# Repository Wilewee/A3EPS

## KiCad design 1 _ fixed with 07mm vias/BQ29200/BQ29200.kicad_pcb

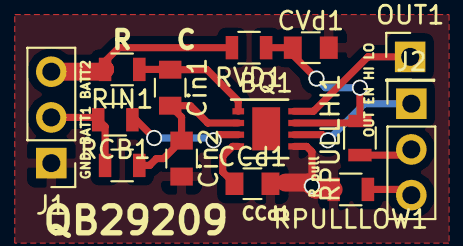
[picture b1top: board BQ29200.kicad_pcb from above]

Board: 2 copper layers, 14 parts (0 on the bottom side), 12 nets.

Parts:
BQ1: BQ29209; DFN-8-1EP_3x3mm_Pitch0.65mm
CCd1: .1u; C_0805
CVd1: .1u; C_0805
Cin1, Cin2: .1u; C_0805
J1, J2: CONN_01X03; Socket_Strip_Straight_1x03_Pitch2.54mm
OUT1: CONN_01X01; Socket_Strip_Straight_1x01_Pitch2.54mm
RCB1: 120; R_0805
RIN1, RIN2: 1k; R_0805
RPULLHI1: R; R_0805
RPULLLOW1: R; R_0805
RVD1: 100; R_0805

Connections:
GND: BQ1.5, CCd1.2, CVd1.2, Cin2.2, J1.1, RPULLLOW1.2
unnamed: BQ1.1, Cin1.1, RIN1.1
unnamed: BQ1.2, Cin1.2, Cin2.1, RIN2.1
unnamed: BQ1.3, RCB1.1
unnamed: BQ1.4, CCd1.1
unnamed: BQ1.6, J2.1
unnamed: BQ1.7, CVd1.1, RPULLHI1.2, RVD1.1
unnamed: BQ1.8, OUT1.1
unnamed: J1.2, RCB1.2, RIN2.2
unnamed: J1.3, RIN1.2, RVD1.2
unnamed: J2.2, RPULLHI1.1
unnamed: J2.3, RPULLLOW1.1

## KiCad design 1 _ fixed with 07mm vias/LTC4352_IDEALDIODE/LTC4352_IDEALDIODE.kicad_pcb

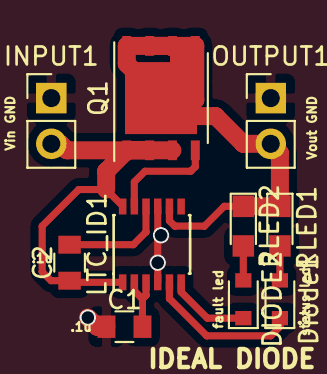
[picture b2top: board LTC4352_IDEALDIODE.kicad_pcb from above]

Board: 2 copper layers, 10 parts (0 on the bottom side), 10 nets.

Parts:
C1, C2: .1u; C_0805
DIODE2: LED; D_0805
Diode1: LED; D_0805
INPUT1: CONN_01X02; Socket_Strip_Straight_1x02_Pitch2.54mm
LTC_ID1: LTC4352; MSOP-12_3x4mm_Pitch0.65mm
OUTPUT1: CONN_01X02; Socket_Strip_Straight_1x02_Pitch2.54mm
Q1: FDMS8050; DFN-8-1EP_6x5mm_Pitch1.27mm_LargeFlag
RLED1, RLED2: 4.7k; LED_0805

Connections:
GND: C1.1, INPUT1.1, LTC_ID1.4, LTC_ID1.7, LTC_ID1.9, OUTPUT1.1
unnamed: C1.2, LTC_ID1.2, LTC_ID1.3
unnamed: C2.1, INPUT1.2, LTC_ID1.1, LTC_ID1.12, Q1.1, Q1.2, Q1.3
unnamed: C2.2, LTC_ID1.10
unnamed: DIODE2.1, LTC_ID1.6
unnamed: DIODE2.2, RLED2.2
unnamed: Diode1.1, LTC_ID1.5
unnamed: Diode1.2, RLED1.2
unnamed: LTC_ID1.8, OUTPUT1.2, Q1.5, Q1.6, Q1.7, Q1.8, RLED1.1, RLED2.1
unnamed: LTC_ID1.11, Q1.4

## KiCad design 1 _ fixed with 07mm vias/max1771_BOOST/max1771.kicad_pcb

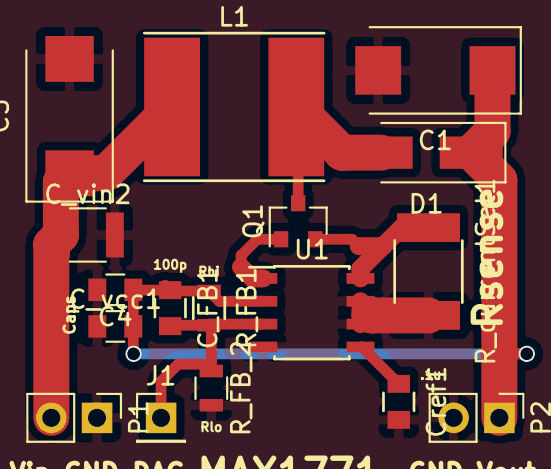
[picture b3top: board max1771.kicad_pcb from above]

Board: 2 copper layers, 17 parts (0 on the bottom side), 8 nets.

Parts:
C1, C5: CP; CP_Tantalum_Case-D_EIA-7343-31_Reflow
C4: C; C_0805
C_FB1: 100p; C_0805
C_vcc1: 1u; C_0805
C_vin2: BIG; C_1210
Cref1: 0.1u; C_0805
D1: D_Schottky_Small; SMA_Handsoldering
J1: CONN_01X01; Socket_Strip_Straight_1x01_Pitch2.54mm
L1: INDUCTOR; Inductor_Taiyo-Yuden_NR-80xx_HandSoldering
P1: Input_conn; Socket_Strip_Straight_1x02_Pitch2.54mm
P2: CONN_01X02; Socket_Strip_Straight_1x02_Pitch2.54mm
Q1: BS170; SOT-23
R_FB1: R_FB_high; R_0805
R_FB_2: R_FB_LOW; R_0805
R_currentSet1: 0.02; R_1812
U1: MAX1771§; SOIC-8_3.9x4.9mm_Pitch1.27mm

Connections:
GND: C1.2, C4.2, C5.2, C_vcc1.1, C_vin2.2, Cref1.2, P1.1, P2.2, R_FB_2.2, R_currentSet1.2, U1.4, U1.6, U1.7
unnamed: C1.1, C4.1, C_FB1.1, C_vcc1.2, D1.1, P2.1, R_FB1.1, U1.2
unnamed: C5.1, C_vin2.1, L1.1, P1.2
unnamed: C_FB1.2, J1.1, R_FB1.2, R_FB_2.1, U1.3
unnamed: Cref1.1, U1.5
unnamed: D1.2, L1.2, Q1.2
unnamed: Q1.1, U1.1
unnamed: Q1.3, R_currentSet1.1, U1.8

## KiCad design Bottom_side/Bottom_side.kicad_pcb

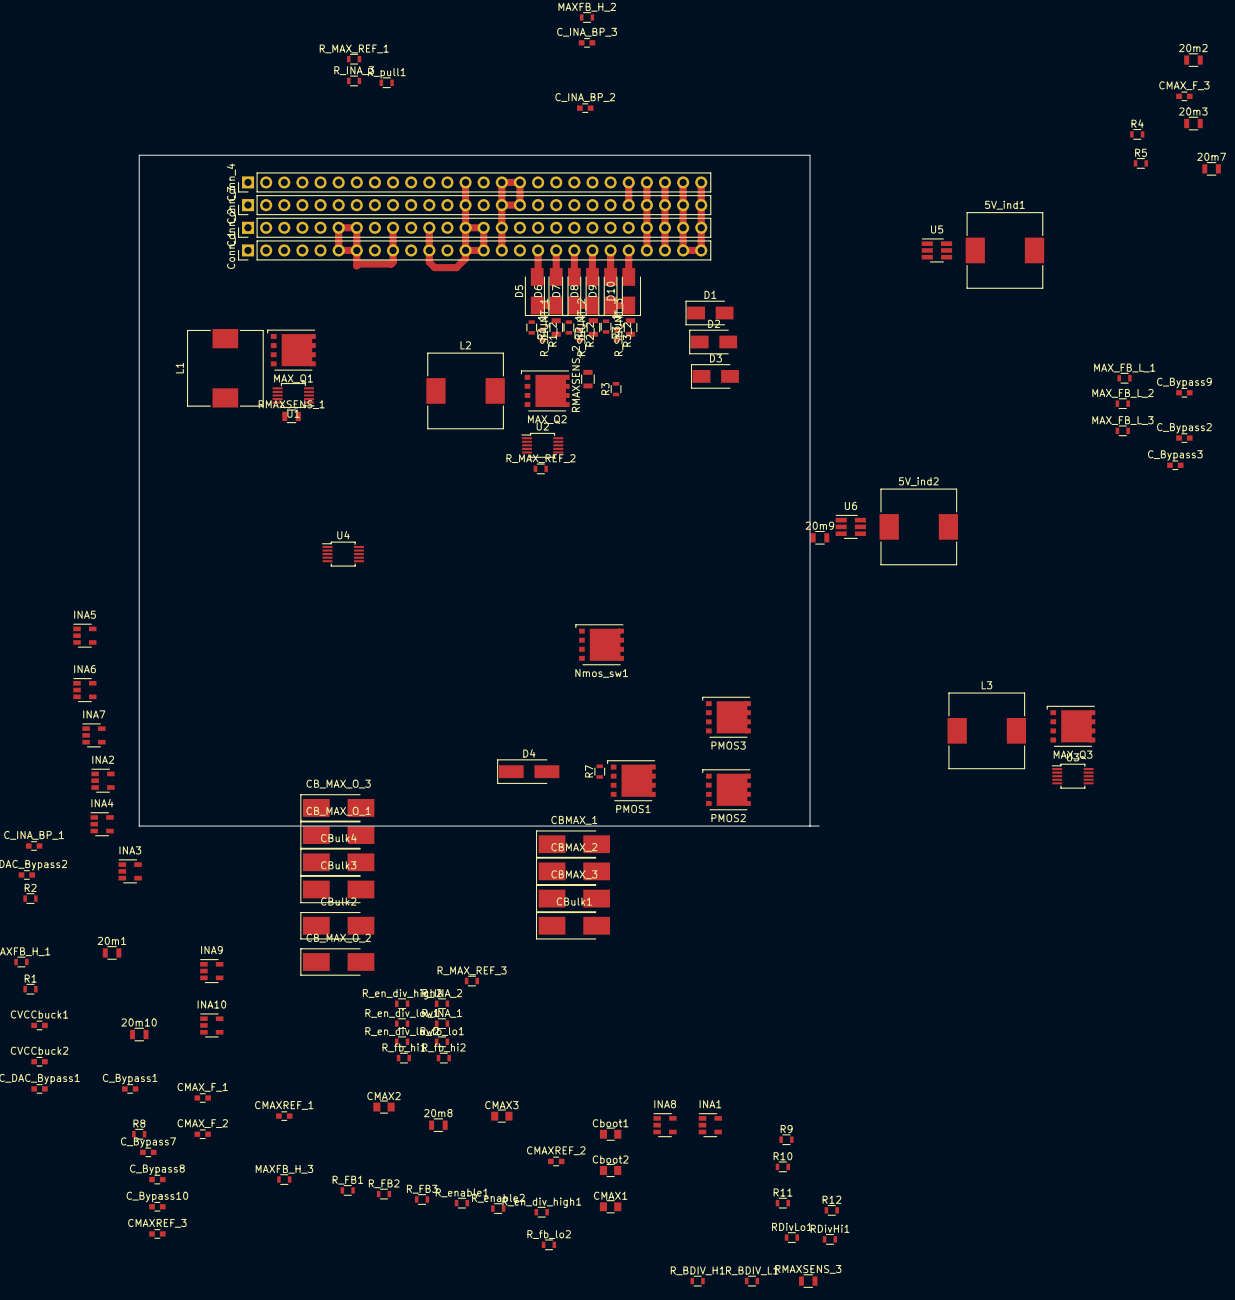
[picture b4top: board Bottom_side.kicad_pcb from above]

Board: 2 copper layers, 95.2 x 94.0 mm, 137 parts (0 on the bottom side), 82 nets.

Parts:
5V_ind1, 5V_ind2: 10u; L_10.4x10.4_H4.8
20m1, 20m2, 20m3, 20m7, 20m8, 20m9, 20m10: R_Shunt; R_0805
CBMAX_1, CBMAX_2, CBMAX_3: 68uF; CP_Tantalum_Case-C_EIA-6032-28_Hand
CB_MAX_O_1, CB_MAX_O_2, CB_MAX_O_3: 68uF; CP_Tantalum_Case-C_EIA-6032-28_Hand
CBulk1, CBulk2, CBulk3, CBulk4: C; CP_Tantalum_Case-C_EIA-6032-28_Hand
CMAX1, CMAX2, CMAX3: 1uF; C_0805
CMAXREF_1, CMAXREF_2, CMAXREF_3: .22uF; C_0603
CMAX_F_1, CMAX_F_2, CMAX_F_3: 220pF; C_0603
CVCCbuck1, CVCCbuck2: 10u; C_0603
C_Bypass1, C_Bypass2, C_Bypass3, C_Bypass7, C_Bypass8, C_Bypass9, C_Bypass10: .1u; C_0603
C_DAC_Bypass1, C_DAC_Bypass2: C; C_0603
C_INA_BP_1, C_INA_BP_2, C_INA_BP_3: .1u; C_0603
Cboot1, Cboot2: .1uF; C_0805
Conn_1, Conn_3: Conn_01x26; Socket_Strip_Straight_1x26_Pitch2.54mm
Conn_2: Conn_2; Socket_Strip_Straight_1x26_Pitch2.54mm
Conn_4: Conn_4; Socket_Strip_Straight_1x26_Pitch2.54mm
D1, D2, D3: D_Schottky; D_SMA
D4: D; D_SMA_Handsoldering
D5, D6, D7, D8, D9, D10: D; D_SMA
INA1, INA2, INA3, INA4, INA5, INA6, INA7, INA8, INA9, INA10: INA139; SOT-23-5
L1, L2, L3: L_Small; L_10.4x10.4_H4.8
MAXFB_H_1, MAXFB_H_2, MAXFB_H_3: 100k; R_0603
MAX_FB_L_1, MAX_FB_L_2, MAX_FB_L_3: 22k; R_0603
MAX_Q1, MAX_Q2, MAX_Q3: Q_NMOS_GDS; TDSON-8-1
Nmos_sw1: Logic level Nch mosfet; TDSON-8-1
PMOS1: PCH GDS; TDSON-8-1
PMOS2, PMOS3: Pch GDS; TDSON-8-1
R1, R2: 10k; R_0603
R1_1, R2_1, R3, R3_1, R4, R5, R9, R10, R11, R12: 100k; R_0603
R1_2, R2_2, R3_2: 200k; R_0603
R7, R8: R; R_0603
RDivHi1: R; R_0603
RDivLo1: R; R_0603
RMAXSENS_1, RMAXSENS_2, RMAXSENS_3: 0.02; R_0805
R_BDIV_H1: 220k; R_0603
R_BDIV_L1: 100k; R_0603
R_FB1, R_FB2, R_FB3: 100k; R_0603
R_INA_1, R_INA_2, R_INA_3: 100k; R_0603
R_MAX_REF_1, R_MAX_REF_2, R_MAX_REF_3: 100k; R_0603
R_SHUNT_1, R_SHUNT_2, R_SHUNT_3: 20m; R_0805
R_en_div_high1, R_en_div_high2: R; R_0603
R_en_div_low1, R_en_div_low2: R; R_0603
R_enable1, R_enable2: R; R_0603
R_fb_hi1, R_fb_hi2: R; R_0603
R_fb_lo1, R_fb_lo2: R; R_0603
R_pull1: R; R_0603
U1, U2, U3: MAX668; MSOP-10_3x3mm_Pitch0.5mm
U4: MCP4728; MSOP-10_3x3mm_Pitch0.5mm
U5, U6: TPS54302; SOT-23-6_Handsoldering

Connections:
/3V3: C_Bypass1.1, C_Bypass2.1, C_Bypass3.1, C_Bypass7.1, C_Bypass8.1, C_Bypass9.1, C_Bypass10.1, C_DAC_Bypass1.1, C_DAC_Bypass2.1, C_INA_BP_1.1, C_INA_BP_2.1, C_INA_BP_3.1, INA1.5, INA2.5, INA3.5, INA4.5, INA5.5, INA6.5, INA7.5, INA8.5, INA9.5, INA10.5, R1.2, R2.2, U4.1
/5V_1: 20m7.1, INA7.4
/5V_2: 20m8.1, INA8.4
/A_1_I: INA1.1, R_INA_1.1
/A_1_O: INA6.1, R5.1
/A_2_I: INA2.1, R_INA_2.1
/A_3_I: INA3.1, R_INA_3.1
/A_3_O: INA4.1, R3.1
/B+: D4.1, PMOS2.2, RDivHi1.2, R_pull1.2
/Batt_V_1: 20m9.1, INA9.4
/Batt_V_2: 20m10.1, INA10.4
/Batt_voltage_divided: R_BDIV_H1.2, R_BDIV_L1.1
/Connectors/5V_1: Conn_1.6, Conn_1.7, Conn_1.9, Conn_2.6, Conn_2.7, Conn_2.9
/Connectors/5V_2: Conn_1.11, Conn_1.13, Conn_1.14, Conn_2.11, Conn_2.13, Conn_2.14, Conn_3.13, Conn_4.13
/Connectors/Batt_TEMP1: Conn_3.22, Conn_4.22
/Connectors/Batt_V_1: Conn_1.23, Conn_2.23, Conn_3.23, Conn_4.23
/Connectors/Batt_V_2: Conn_1.25, Conn_1.26, Conn_2.25, Conn_2.26, Conn_3.25, Conn_3.26, Conn_4.25, Conn_4.26
/Curr_5V_1: INA7.1, R9.1
/Curr_5V_2: INA8.1, R10.1
/Curr_Vbat_1: INA9.1, R11.1
/Curr_Vbat_2: INA10.1, R12.1
/Input/Boost_Converters/I_in_1: CBMAX_1.1, INA1.4, L1.1, R_SHUNT_1.1
/Input/Boost_Converters/I_in_2: CBMAX_2.1, INA2.4, L2.1, R_SHUNT_2.1
/Input/Boost_Converters/I_in_3: CBMAX_3.1, INA3.4, L3.1, R_SHUNT_3.1
/Input/Boost_Converters/MAX668/FB: CMAX_F_1.1, CMAX_F_2.1, CMAX_F_3.1, MAXFB_H_1.2, MAXFB_H_2.2, MAXFB_H_3.2, MAX_FB_L_1.1, MAX_FB_L_2.1, MAX_FB_L_3.1, R_FB1.1, R_FB2.1, R_FB3.1, U1.5, U2.5, U3.5
/Input/DAC/Dac_1: R_FB1.2, U4.6
/Input/DAC/Dac_2: R_FB2.2, U4.7
/Input/DAC/Dac_3: R_FB3.2, U4.8
/Input/InaOutput/INA_out/Ina_Analog: INA5.1, R4.1
/Input/InaOutput/I_in_1: 20m1.2, CB_MAX_O_1.1, D1.1, INA4.3, MAXFB_H_1.1, U1.9, U1.10
/Input/InaOutput/I_in_2: 20m2.2, CB_MAX_O_2.1, D2.1, INA5.3, MAXFB_H_2.1, U2.9, U2.10
/Input/InaOutput/I_in_3: 20m3.2, CB_MAX_O_3.1, D3.1, INA6.3, MAXFB_H_3.1, U3.9, U3.10
/Input/Output_1: 20m1.1, 20m2.1, 20m3.1, INA4.4, INA5.4, INA6.4, PMOS1.2, R7.1, R_BDIV_H1.1
/Input/SCL: R2.1, U4.2
/Input/SDA: R1.1, U4.3
/MCU_POWER_SW: Nmos_sw1.1, RDivHi1.1, RDivLo1.2
/OUTPUT/5VBuck/5V_OUT: 5V_ind1.2, 5V_ind2.2, 20m7.2, 20m8.2, CBulk1.1, CBulk2.1, CBulk3.1, CBulk4.1, INA7.3, INA8.3, R_fb_hi1.1, R_fb_hi2.1
/OUTPUT/POWER_INPUT: 20m9.2, 20m10.2, CVCCbuck1.1, CVCCbuck2.1, INA9.3, INA10.3, PMOS3.3, R_en_div_high1.1, R_en_div_high2.1, U5.3, U6.3
/RBF1: PMOS1.1, R7.2
/V1: R1_1.2, R1_2.1
/V2: R2_1.2, R2_2.1
/V3: R3_1.2, R3_2.1
GND: CBMAX_1.2, CBMAX_2.2, CBMAX_3.2, CB_MAX_O_1.2, CB_MAX_O_2.2, CB_MAX_O_3.2, CBulk1.2, CBulk2.2, CBulk3.2, CBulk4.2, CMAX1.2, CMAX2.2, CMAX3.2, CMAXREF_1.2, CMAXREF_2.2, CMAXREF_3.2, CMAX_F_1.2, CMAX_F_2.2, CMAX_F_3.2, CVCCbuck1.2, CVCCbuck2.2, C_Bypass1.2, C_Bypass2.2, C_Bypass3.2, C_Bypass7.2, C_Bypass8.2, C_Bypass9.2, C_Bypass10.2, C_DAC_Bypass1.2, C_DAC_Bypass2.2, C_INA_BP_1.2, C_INA_BP_2.2, C_INA_BP_3.2, Conn_1.3, Conn_1.8, Conn_1.10, Conn_1.12, Conn_1.15, Conn_1.24, Conn_2.3, Conn_2.8, Conn_2.10, Conn_2.12, Conn_2.15, Conn_2.17, Conn_2.18, Conn_2.19, Conn_2.20, Conn_2.21, Conn_2.24, Conn_3.3, Conn_3.4, Conn_3.15, Conn_3.16, Conn_3.24, Conn_4.3, Conn_4.4, Conn_4.9, Conn_4.15, Conn_4.16, Conn_4.21, Conn_4.24, INA1.2, INA2.2, INA3.2, INA4.2, INA5.2, INA6.2, INA7.2, INA8.2, INA9.2, INA10.2, MAX_FB_L_1.2, MAX_FB_L_2.2, MAX_FB_L_3.2, R1_2.2, R2_2.2, R3.2, R3_2.2, R4.2, R5.2, R9.2, R10.2, R11.2, R12.2, RDivLo1.1, RMAXSENS_1.2, RMAXSENS_2.2, RMAXSENS_3.2, R_BDIV_L1.2, R_INA_1.2, R_INA_2.2, R_INA_3.2, R_MAX_REF_1.2, R_MAX_REF_2.2, R_MAX_REF_3.2, R_en_div_low1.2, R_en_div_low2.2, R_fb_lo1.2, R_fb_lo2.2, U1.3, U1.7, U2.3, U2.7, U3.3, U3.7, U4.10, U5.1, U6.1
unnamed: 5V_ind1.1, Cboot1.2, U5.2
unnamed: 5V_ind2.1, Cboot2.2, U6.2
unnamed: CMAX1.1, U1.1
unnamed: CMAX2.1, U2.1
unnamed: CMAX3.1, U3.1
unnamed: CMAXREF_1.1, U1.4
unnamed: CMAXREF_2.1, U2.4
unnamed: CMAXREF_3.1, U3.4
unnamed: Cboot1.1, U5.6
unnamed: Cboot2.1, U6.6
unnamed: Conn_1.17, D5.2
unnamed: Conn_1.18, D6.2
unnamed: Conn_1.19, D7.2
unnamed: Conn_1.20, D8.2
unnamed: Conn_1.21, D9.2
unnamed: Conn_1.22, D10.2
unnamed: D1.2, L1.2, MAX_Q1.2
unnamed: D2.2, L2.2, MAX_Q2.2
unnamed: D3.2, L3.2, MAX_Q3.2
unnamed: D4.2, PMOS1.3
unnamed: MAX_Q1.1, U1.8
unnamed: MAX_Q1.3, RMAXSENS_1.1, U1.6
unnamed: MAX_Q2.1, U2.8
unnamed: MAX_Q2.3, RMAXSENS_2.1, U2.6
unnamed: MAX_Q3.1, U3.8
unnamed: MAX_Q3.3, RMAXSENS_3.1, U3.6
unnamed: Nmos_sw1.2, R8.1
unnamed: Nmos_sw1.3, PMOS2.1, PMOS3.1, R_pull1.1
unnamed: PMOS2.3, PMOS3.2
unnamed: R_MAX_REF_1.1, U1.2
unnamed: R_MAX_REF_2.1, U2.2
unnamed: R_MAX_REF_3.1, U3.2
unnamed: R_en_div_high1.2, R_en_div_low1.1, R_enable1.1, U5.5
unnamed: R_en_div_high2.2, R_en_div_low2.1, R_enable2.1, U6.5
unnamed: R_fb_hi1.2, R_fb_lo1.1, U5.4
unnamed: R_fb_hi2.2, R_fb_lo2.1, U6.4
X+: D5.1, D6.1, INA1.3, R1_1.1, R_SHUNT_1.2
Y+: D7.1, D8.1, INA2.3, R2_1.1, R_SHUNT_2.2
Z+: D9.1, D10.1, INA3.3, R3_1.1, R_SHUNT_3.2

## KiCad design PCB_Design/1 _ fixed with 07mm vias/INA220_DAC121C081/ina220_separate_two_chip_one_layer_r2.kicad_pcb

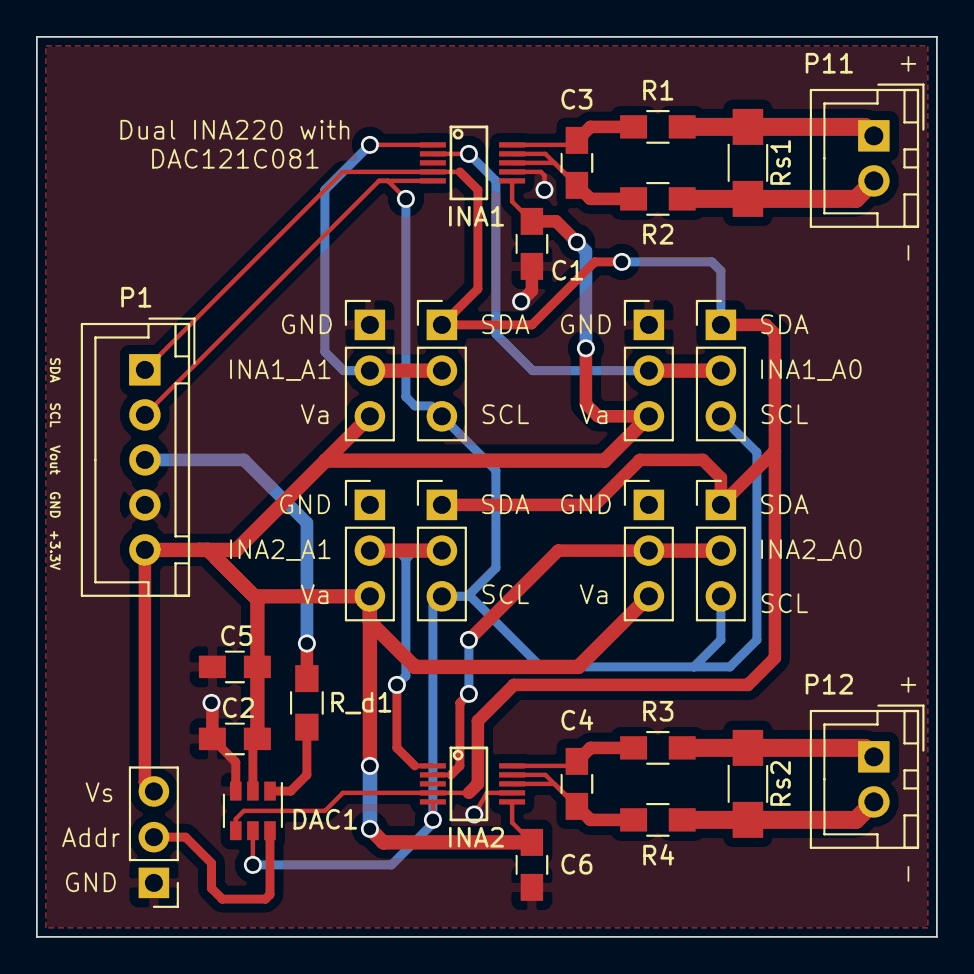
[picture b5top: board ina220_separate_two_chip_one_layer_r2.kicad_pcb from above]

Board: 2 copper layers, 50.0 x 50.0 mm, 28 parts (0 on the bottom side), 19 nets.

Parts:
C1, C2, C3, C4, C6: 0.1u; C_0805_HandSoldering
C5: 4.7u; C_0805_HandSoldering
DAC1: DAC121C081; SOT-23-6
INA1, INA2: INA220; ina220__smd_footprint
P1: CONN_01X05; JST_XH_B05B-XH-A_05x2.50mm_Straight
P2, P3: INA1_A0; Pin_Header_Straight_1x03_Pitch2.54mm
P4, P5: INA1_A1; Pin_Header_Straight_1x03_Pitch2.54mm
P6, P7: INA2_A0; Pin_Header_Straight_1x03_Pitch2.54mm
P8, P9: INA2_A1; Pin_Header_Straight_1x03_Pitch2.54mm
P10: DAC_ADDR; Pin_Header_Straight_1x03_Pitch2.54mm
P11, P12: CONN_01X02; JST_XH_B02B-XH-A_02x2.50mm_Straight
R1, R2, R3, R4: 10; R_0805_HandSoldering
R_d1: 300k; R_0805_HandSoldering
Rs1, Rs2: 20m; R_1206_HandSoldering

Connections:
ADR0: DAC1.6, P10.2
GND: C1.2, C2.2, C5.2, C6.2, DAC1.3, INA1.7, INA2.7, P1.4, P2.1, P4.1, P6.1, P8.1, P10.1
IN1+: C3.1, INA1.10, R1.2
IN1-: C3.2, INA1.8, INA1.9, R2.2
IN2+: C4.1, INA2.10, R3.2
IN2-: C4.2, INA2.8, INA2.9, R4.2
INA1_A0: INA1.2, P2.2, P3.2
INA1_A1: INA1.1, P4.2, P5.2
INA2_A0: INA2.2, P6.2, P7.2
INA2_A1: INA2.1, P8.2, P9.2
unnamed: DAC1.1, R_d1.1
SCL: DAC1.5, INA1.5, INA2.5, P1.2, P3.3, P5.3, P7.3, P9.3
SDA: DAC1.4, INA1.4, INA2.4, P1.1, P3.1, P5.1, P7.1, P9.1
Shunt1+: P11.1, R1.1, Rs1.1
Shunt1-: P11.2, R2.1, Rs1.2
Shunt2+: P12.1, R3.1, Rs2.1
Shunt2-: P12.2, R4.1, Rs2.2
Va: C1.1, C2.1, C5.1, C6.1, DAC1.2, INA1.6, INA2.6, P1.5, P2.3, P4.3, P6.3, P8.3, P10.3
Vout: P1.3, R_d1.2
